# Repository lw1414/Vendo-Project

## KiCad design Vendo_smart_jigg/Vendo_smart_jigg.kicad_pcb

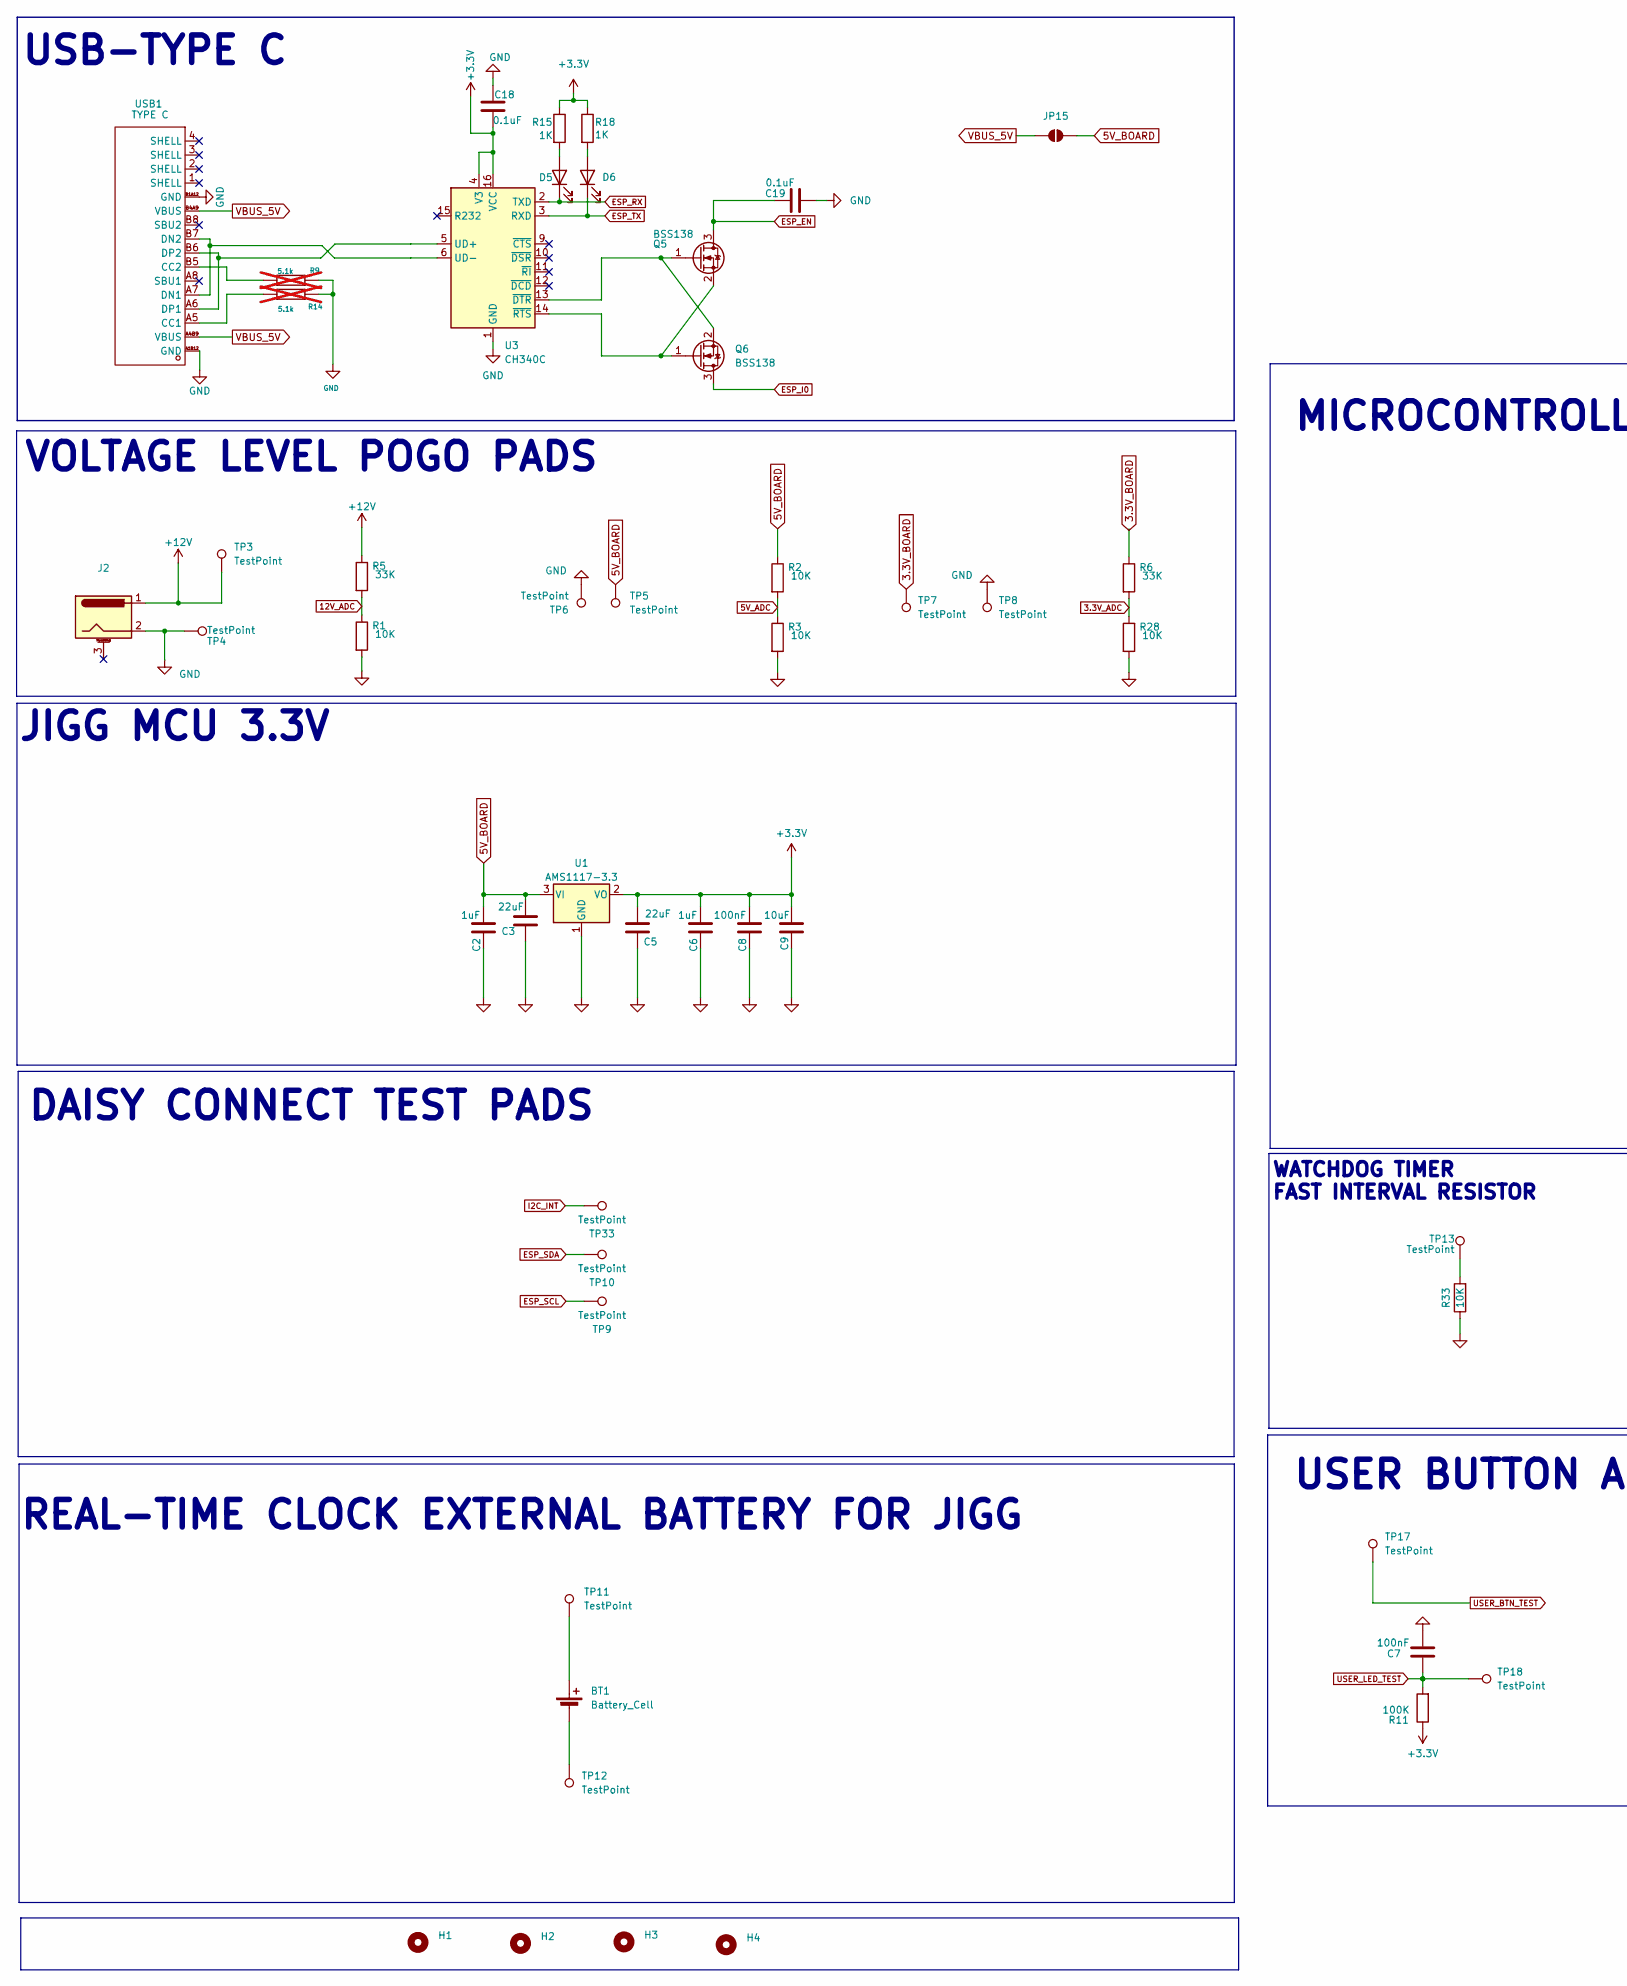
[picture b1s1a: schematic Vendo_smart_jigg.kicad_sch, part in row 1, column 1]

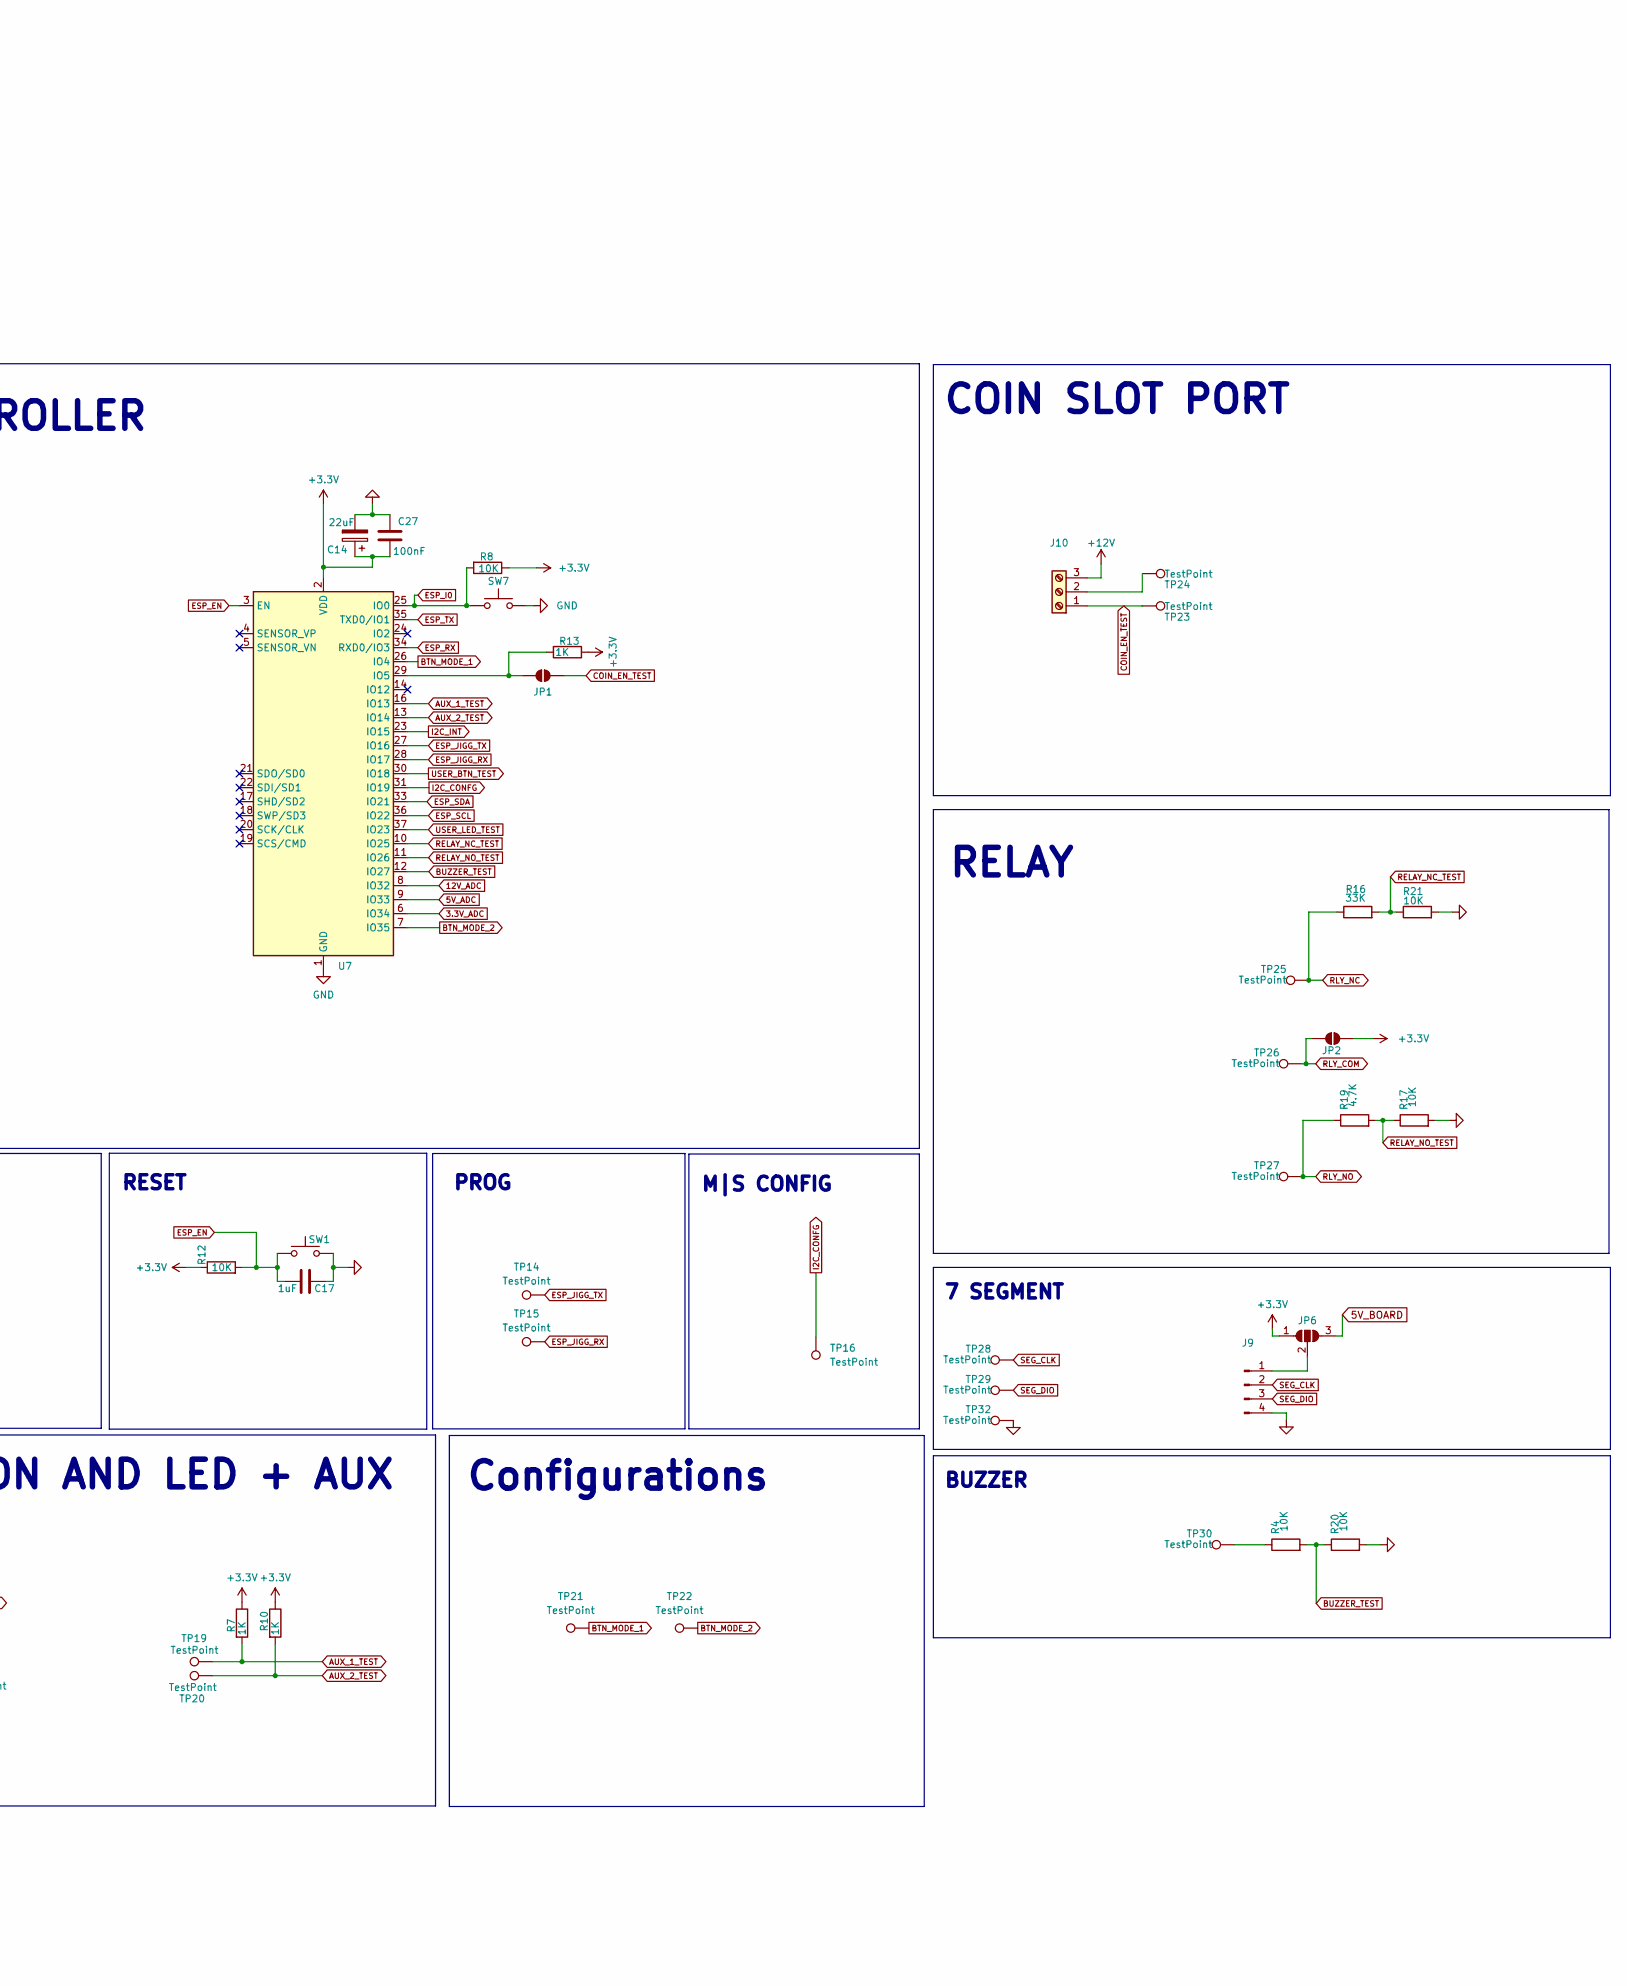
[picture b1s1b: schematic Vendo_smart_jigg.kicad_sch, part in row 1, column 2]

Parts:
BT1: Battery_Cell; BAT-TH_CR2032-BS-6-1; LCSC C969909
C2, C6: 1uF; C_0805_2012Metric_Pad1.18x1.45mm_HandSolder; LCSC C49678
C3, C5: 22uF; C_0603_1608Metric; LCSC C59461
C7, C8, C27: 100nF; C_0603_1608Metric_Pad1.08x0.95mm_HandSolder; LCSC C14663
C9: 10uF; C_0603_1608Metric_Pad1.08x0.95mm_HandSolder; LCSC C85713
C14: 22uF; C_0603_1608Metric_Pad1.08x0.95mm_HandSolder; LCSC C59461
C17: 1uF; C_0603_1608Metric_Pad1.08x0.95mm_HandSolder; LCSC C14663
C18: 0.1uF; C_0805_2012Metric_Pad1.18x1.45mm_HandSolder
C19: 0.1uF; C_0805_2012Metric_Pad1.18x1.45mm_HandSolder; LCSC C49678
D5, D6: LED; LED_0805_2012Metric_Pad1.15x1.40mm_HandSolder; LCSC C2297
H1, H2, H3, H4: MountingHole; MountingHole_3.2mm_M3_DIN965_Pad_TopBottom
J2: Barrel_Jack_MountingPin; BarrelJack_GCT_DCJ200-10-A_Horizontal
J9: Conn_01x04_Pin; JST_EH_B4B-EH-A_1x04_P2.50mm_Vertical
J10: Screw_Terminal_01x03; TerminalBlock_Xinya_XY308-2.54-3P_1x03_P2.54mm_Horizontal
JP1, JP2, JP15: SolderJumper_2_Open; PinHeader_1x02_P2.54mm_Vertical
JP6: SolderJumper_3_Open; SolderJumper-3_P1.3mm_Open_Pad1.0x1.5mm_NumberLabels
Q5, Q6: BSS138; SOT-23; LCSC C426569
R1, R2, R3, R4, R8, R12, R17, R20, R21, R28: 10K; R_0603_1608Metric_Pad0.98x0.95mm_HandSolder; LCSC C21190
R5, R6, R16: 33K; R_0603_1608Metric_Pad0.98x0.95mm_HandSolder; LCSC C21190
R7, R10, R13: 1K; R_0603_1608Metric_Pad0.98x0.95mm_HandSolder; LCSC C2960810
R9, R14: 5.1k; R_0603_1608Metric_Pad0.98x0.95mm_HandSolder; LCSC C103079; not fitted
R11: 100K; R_0603_1608Metric_Pad0.98x0.95mm_HandSolder; LCSC C105574
R15, R18: 1K; R_0603_1608Metric_Pad0.98x0.95mm_HandSolder; LCSC C21190
R19: 4.7K; R_0603_1608Metric_Pad0.98x0.95mm_HandSolder; LCSC C21190
R33: 10K; R_0603_1608Metric_Pad0.98x0.95mm_HandSolder; LCSC C2906982
SW1: SW_Push; SW_SPST_PTS645; LCSC C2689642
SW7: SW_Push; PinHeader_1x02_P2.54mm_Vertical; LCSC C2689642
TP3, TP4, TP5, TP6, TP7, TP8, TP9, TP10, TP11, TP12, TP13, TP16, TP17, TP18, TP19, TP20, TP21, TP22, TP23, TP24, TP25, TP26, TP27, TP30, TP32, TP33: TestPoint; TestPoint_Pad_D2.5mm
TP14, TP15, TP28, TP29: TestPoint; TestPoint_Pad_D1.5mm
U1: AMS1117-3.3; SOT-223-3_TabPin2; LCSC C5199435
U3: CH340C; SOP-16_3.9x9.9mm_P1.27mm; LCSC C84681
U7: ESP32-WROOM-32; ESP32-WROOM-32UE; LCSC C529577
USB1: TYPE C; USB-C-SMD_TYPE-C16PIN; Manufacturer Part TYPE-C16PIN; LCSC Part Name Type-C 母 卧贴

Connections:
3.3V_ADC: R6.2, R28.1, U7.6 (IO34)
3.3V_BOARD: R6.1, TP7.1
5V_ADC: R2.2, R3.1, U7.9 (IO33)
5V_BOARD: C2.2, C3.2, JP6.3 (B), JP15.1 (A), R2.1, TP5.1, U1.3 (VI)
12V_ADC: R1.1, R5.2, U7.8 (IO32)
+3.3V: C5.2, C6.2, C8.2, C9.2, C14.1, C18.1, C27.1, JP2.2 (B), JP6.1 (A), R7.1, R8.1, R10.1, R11.1, R12.1, R13.1, R15.1, R18.1, U1.2 (VO), U3.4 (V3), U3.16 (VCC), U7.2 (VDD)
+12V: J2.1, J10.3, R5.1, TP3.1
AUX_1_TEST: R7.2, TP19.1, U7.16 (IO13)
AUX_2_TEST: R10.2, TP20.1, U7.13 (IO14)
BTN_MODE_1: TP21.1, U7.26 (IO4)
BTN_MODE_2: TP22.1, U7.7 (IO35)
BUZZER_TEST: R4.2, R20.1, U7.12 (IO27)
COIN_EN_TEST: J10.1, JP1.1 (A), TP23.1
ESP_EN: C17.2, C19.2, Q5.3 (D), R12.2, SW1.1, U7.3 (EN)
ESP_I0: Q6.3 (D), R8.2, SW7.1, U7.25 (IO0)
ESP_JIGG_RX: TP15.1, U7.28 (IO17)
ESP_JIGG_TX: TP14.1, U7.27 (IO16)
ESP_RX: D5.1 (K), U3.2 (TXD), U7.34 (RXD0/IO3)
ESP_SCL: TP9.1, U7.36 (IO22)
ESP_SDA: TP10.1, U7.33 (IO21)
ESP_TX: D6.1 (K), U3.3 (RXD), U7.35 (TXD0/IO1)
GND: C2.1, C3.1, C5.1, C6.1, C7.1, C8.1, C9.1, C14.2, C17.1, C18.2, C19.1, C27.2, J2.2, J9.4, R1.2, R3.2, R9.2, R14.2, R17.2, R20.2, R21.2, R28.2, R33.1, SW1.2, SW7.2, TP4.1, TP6.1, TP8.1, TP32.1, U1.1 (GND), U3.1 (GND), U7.1 (GND), U7.15 (GND), U7.38 (GND), U7.39 (GND), USB1.A1B12 (GND), USB1.B1A12 (GND)
I2C_CONFG: TP16.1, U7.31 (IO19)
I2C_INT: TP33.1, U7.23 (IO15)
unnamed: BT1.1 (+), TP11.1
unnamed: BT1.2 (-), TP12.1
unnamed: D5.2 (A), R15.2
unnamed: D6.2 (A), R18.2
unnamed: J9.1, JP6.2 (C)
unnamed: J10.2, TP24.1
unnamed: JP1.2 (B), R13.2, U7.29 (IO5)
unnamed: Q5.1 (G), Q6.2 (S), U3.13 (~DTR)
unnamed: Q5.2 (S), Q6.1 (G), U3.14 (~RTS)
unnamed: R4.1, TP30.1
unnamed: R33.2, TP13.1
unnamed: U3.5 (UD+), USB1.A6 (DP1), USB1.B6 (DP2)
unnamed: U3.6 (UD-), USB1.A7 (DN1), USB1.B7 (DN2)
unnamed: R14.1, USB1.A5 (CC1)
unnamed: R9.1, USB1.B5 (CC2)
RELAY_NC_TEST: R16.2, R21.1, U7.10 (IO25)
RELAY_NO_TEST: R17.1, R19.2, U7.11 (IO26)
RLY_COM: JP2.1 (A), TP26.1
RLY_NC: R16.1, TP25.1
RLY_NO: R19.1, TP27.1
SEG_CLK: J9.2, TP28.1
SEG_DIO: J9.3, TP29.1
USER_BTN_TEST: TP17.1, U7.30 (IO18)
USER_LED_TEST: C7.2, R11.2, TP18.1, U7.37 (IO23)
VBUS_5V: JP15.2 (B), USB1.A4B9 (VBUS), USB1.B4A9 (VBUS)

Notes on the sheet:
DAISY CONNECT TEST PADS
WATCHDOG TIMER FAST INTERVAL RESISTOR
USER BUTTON AND LED + AUX
COIN SLOT PORT
M|S CONFIG
RESET
VOLTAGE LEVEL POGO PADS
7 SEGMENT
Configurations
PROG
RELAY
MICROCONTROLLER
REAL-TIME CLOCK EXTERNAL BATTERY FOR JIGG
BUZZER
JIGG MCU 3.3V
USB-TYPE C

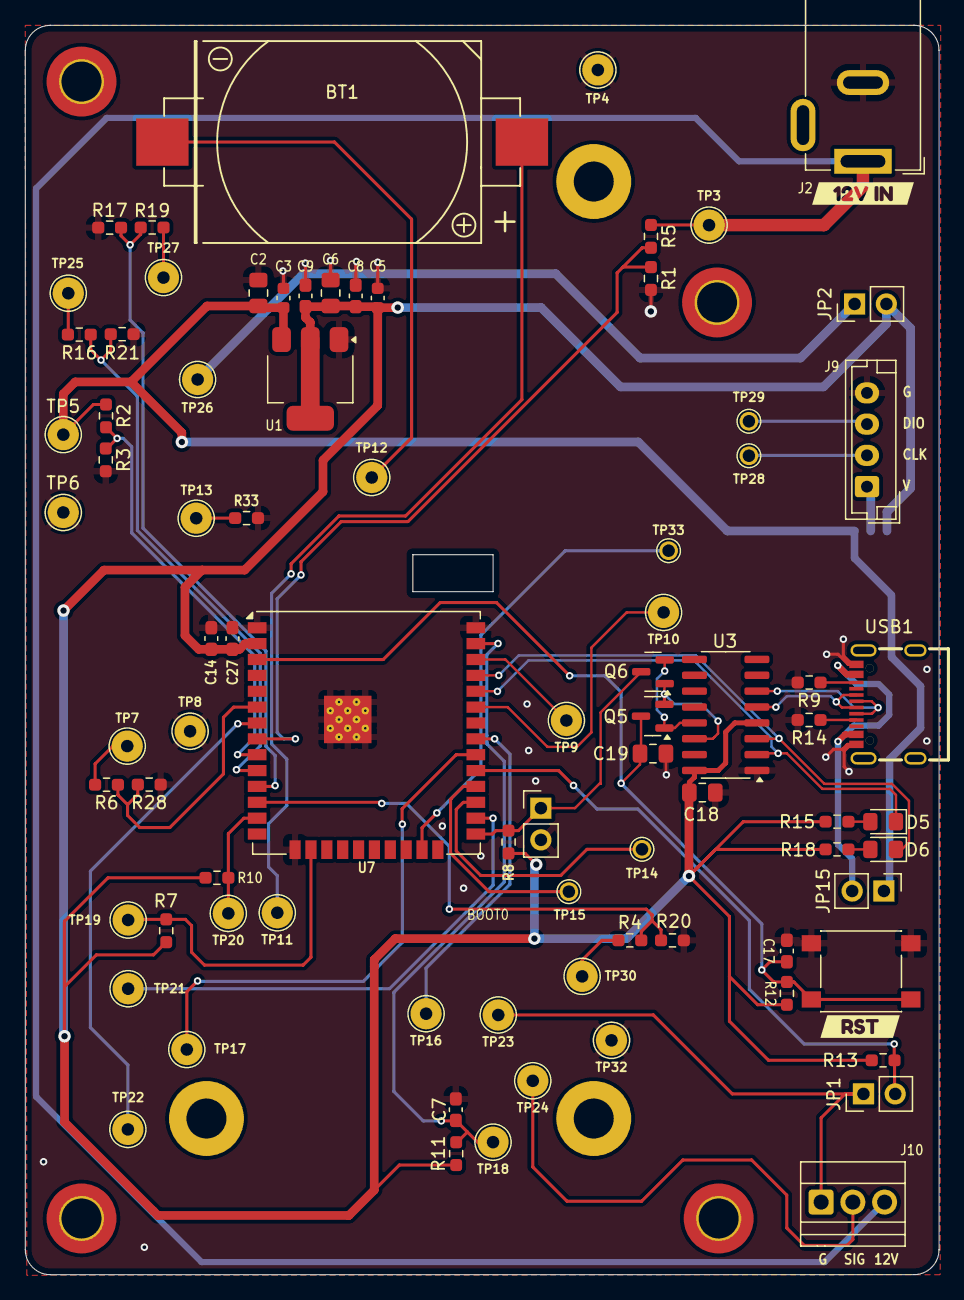
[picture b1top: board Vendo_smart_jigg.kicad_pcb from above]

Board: 2 copper layers, 73.1 x 100.0 mm, 89 parts (1 on the bottom side), 49 nets.

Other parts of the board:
kibuzzard-6A0C536D: G***; kibuzzard-6A0C536D
kibuzzard-6A0C5003: G***; kibuzzard-6A0C5003

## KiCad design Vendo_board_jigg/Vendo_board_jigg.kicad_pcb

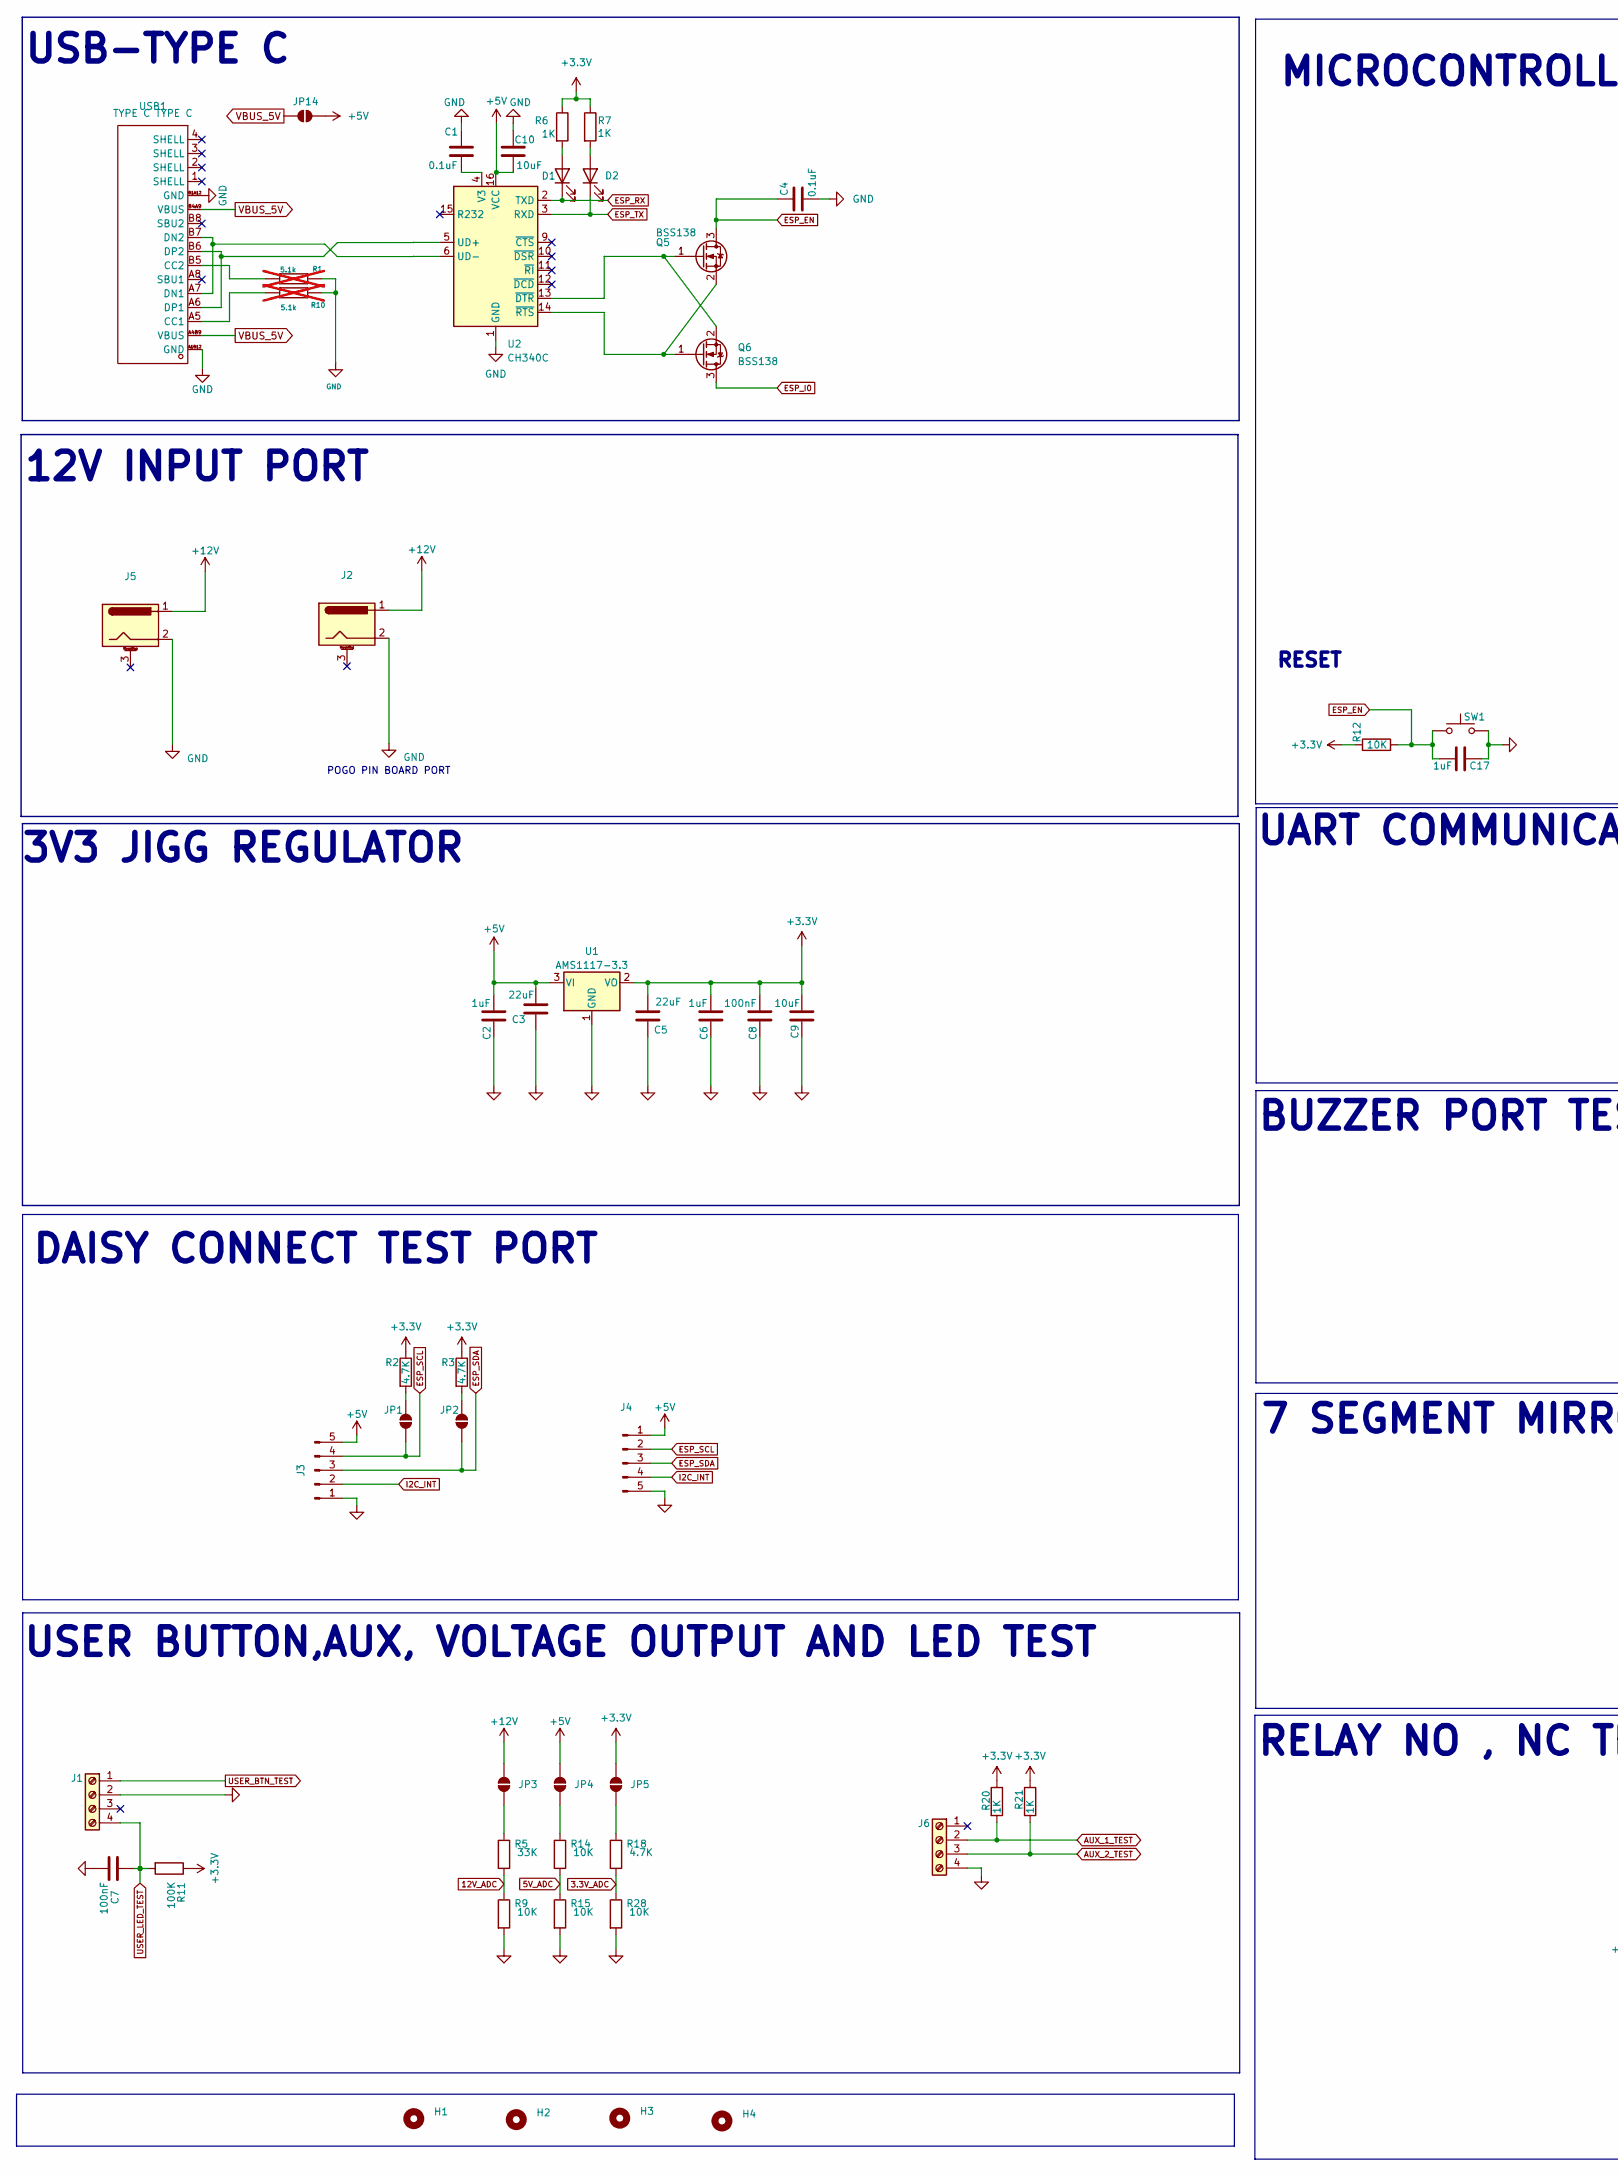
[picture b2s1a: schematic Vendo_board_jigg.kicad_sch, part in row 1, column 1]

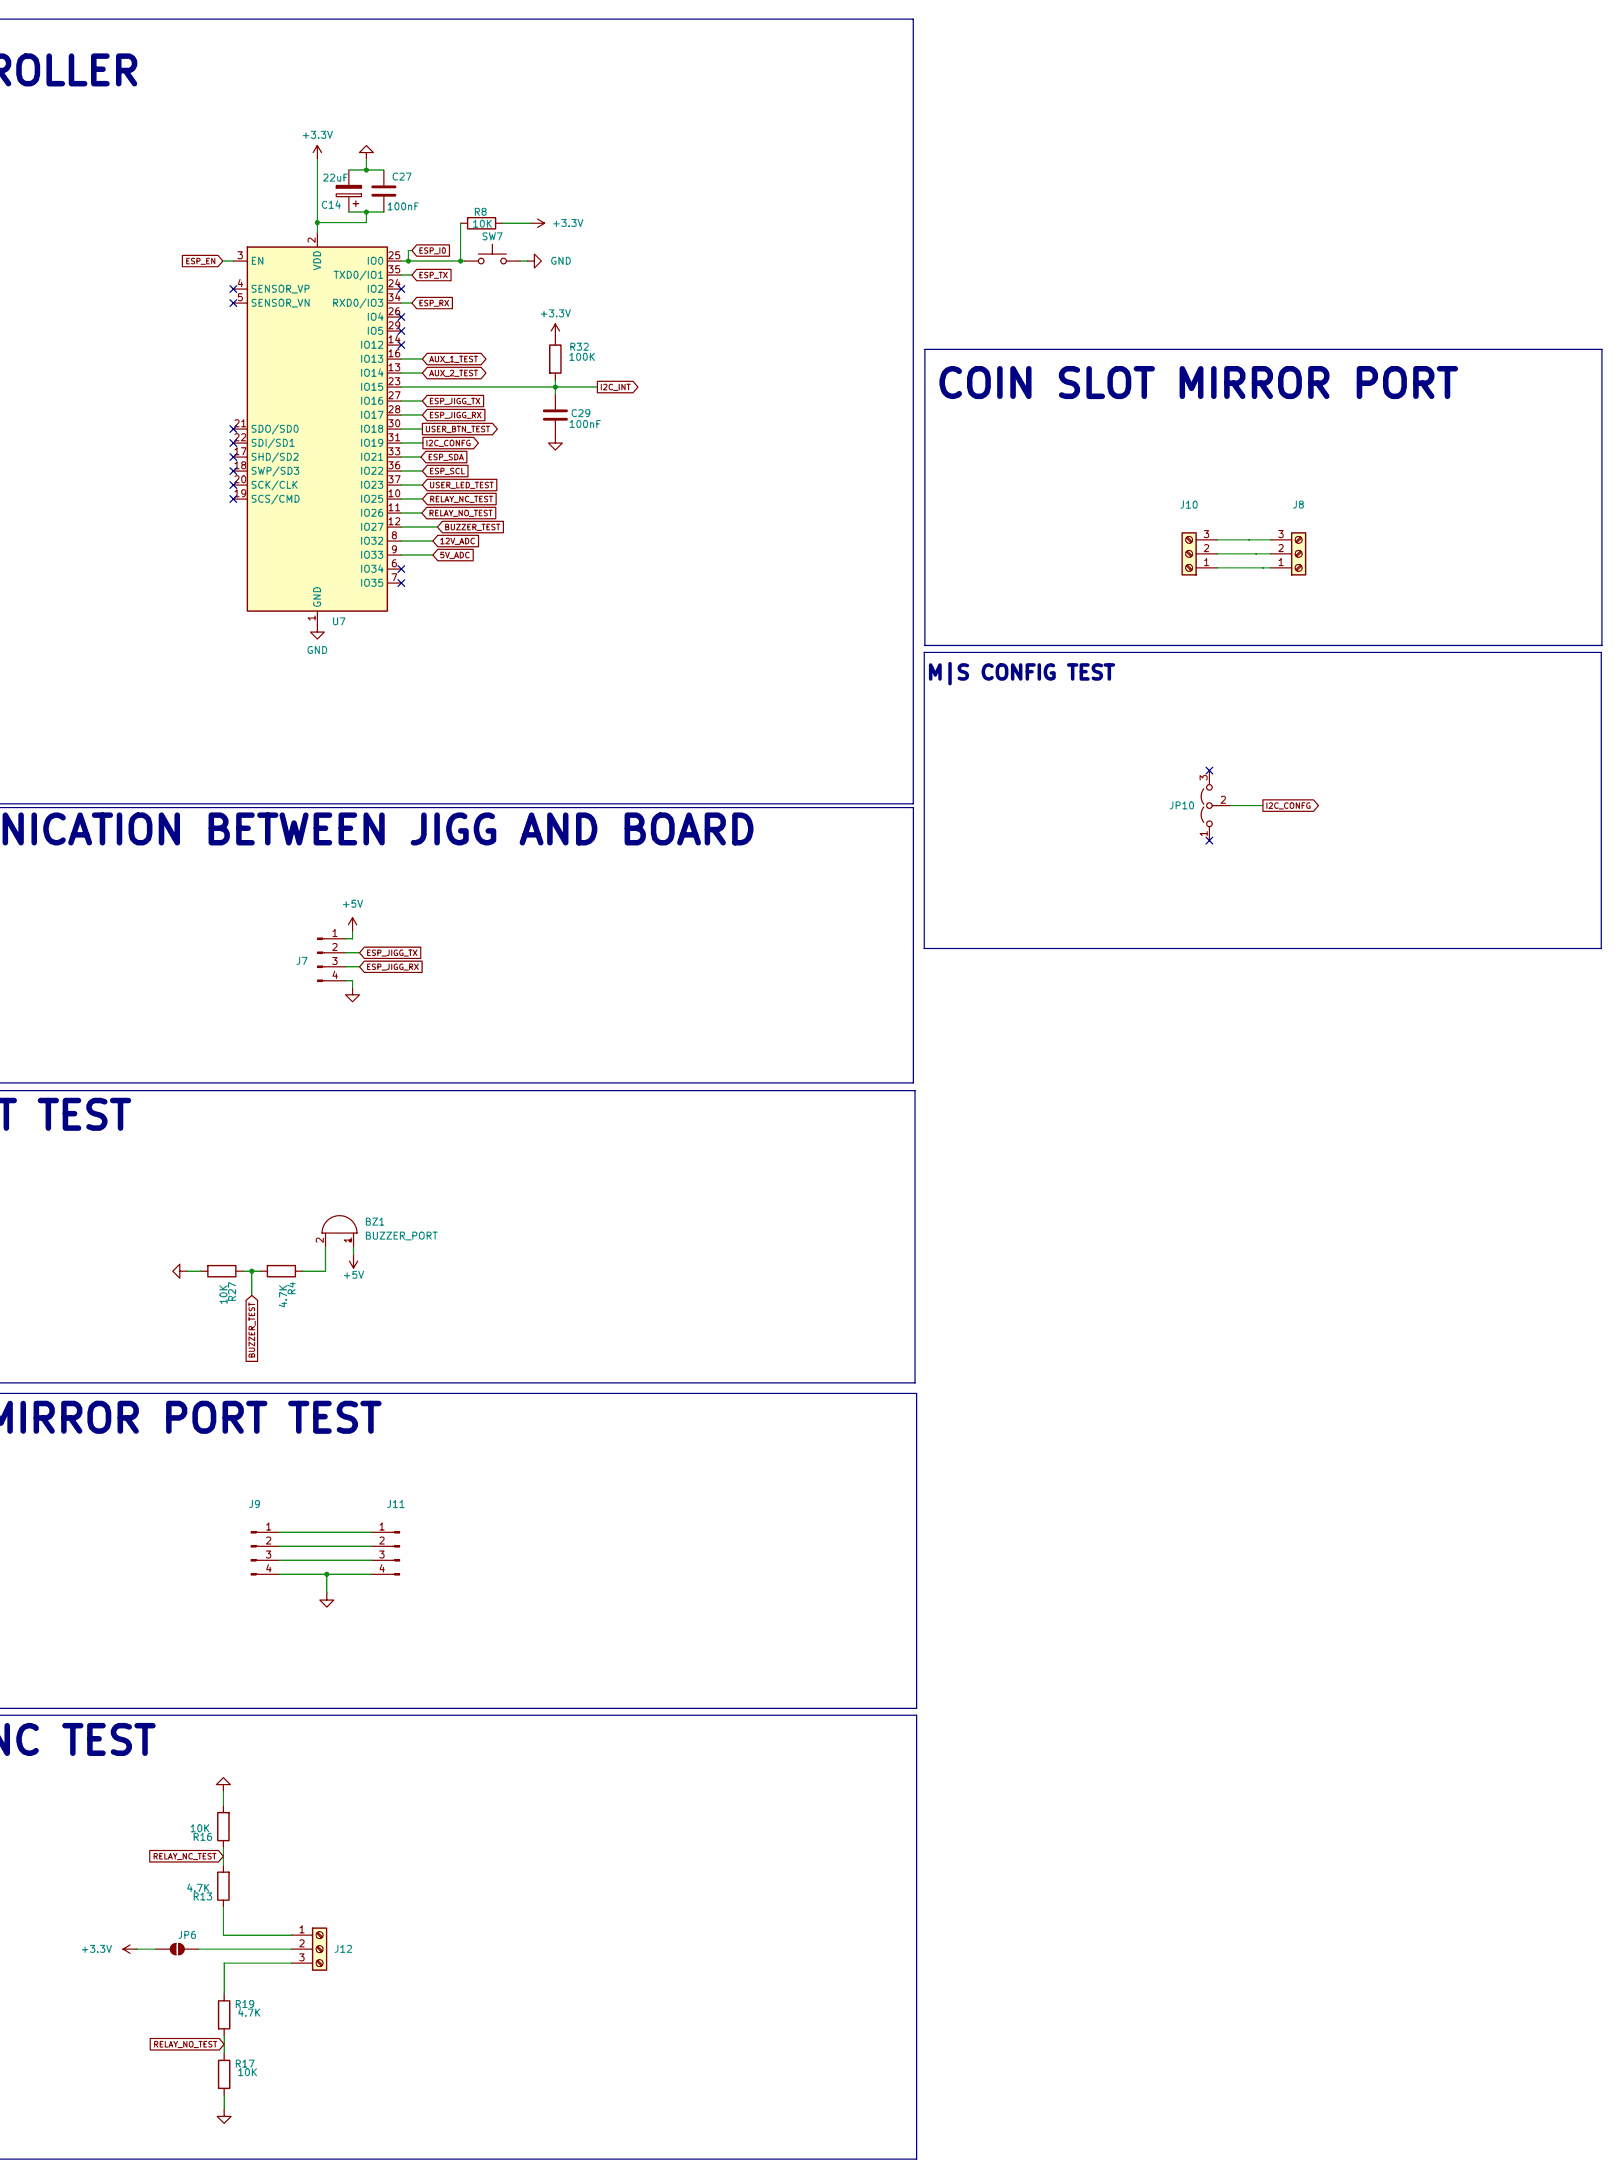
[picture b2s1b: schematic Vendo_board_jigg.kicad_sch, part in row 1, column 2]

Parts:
BZ1: BUZZER_PORT; Buzzer_12x9.5RM7.6
C1, C4: 0.1uF; C_0805_2012Metric_Pad1.18x1.45mm_HandSolder; LCSC C49678
C2, C6: 1uF; C_0805_2012Metric_Pad1.18x1.45mm_HandSolder; LCSC C49678
C3, C5: 22uF; C_0603_1608Metric; LCSC C59461
C7, C8, C27, C29: 100nF; C_0603_1608Metric_Pad1.08x0.95mm_HandSolder; LCSC C14663
C9: 10uF; C_0603_1608Metric_Pad1.08x0.95mm_HandSolder; LCSC C85713
C10: 10uF; C_0805_2012Metric_Pad1.18x1.45mm_HandSolder; LCSC C15850
C14: 22uF; C_0603_1608Metric_Pad1.08x0.95mm_HandSolder; LCSC C59461
C17: 1uF; C_0603_1608Metric_Pad1.08x0.95mm_HandSolder; LCSC C14663
D1, D2: LED; LED_0805_2012Metric_Pad1.15x1.40mm_HandSolder; LCSC C2297
H1, H2, H3, H4: MountingHole; MountingHole_3.2mm_M3_DIN965_Pad_TopBottom
J1, J6: Screw_Terminal_01x04; TerminalBlock_Xinya_XY308-2.54-4P_1x04_P2.54mm_Horizontal
J2, J5: Barrel_Jack_MountingPin; BarrelJack_GCT_DCJ200-10-A_Horizontal
J3, J4: Conn_01x05_Pin; JST_EH_B5B-EH-A_1x05_P2.50mm_Vertical
J7: FTDI; PinHeader_1x04_P2.54mm_Vertical
J8, J10: Screw_Terminal_01x03; TerminalBlock_Xinya_XY308-2.54-3P_1x03_P2.54mm_Horizontal
J9, J11: Conn_01x04_Pin; JST_EH_B4B-EH-A_1x04_P2.50mm_Vertical
J12: Screw_Terminal_01x03; TerminalBlock_MetzConnect_Type073_RT02603HBLU_1x03_P5.08mm_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
JP1, JP2: SolderJumper_2_Open; SolderJumper-2_P1.3mm_Open_RoundedPad1.0x1.5mm
JP3, JP4, JP5, JP6, JP14: SolderJumper_2_Open; PinHeader_1x02_P2.54mm_Vertical
JP10: Jumper_3_Open; PinHeader_1x03_P2.54mm_Vertical
Q5, Q6: BSS138; SOT-23; LCSC C426569
R1, R10: 5.1k; R_0603_1608Metric_Pad0.98x0.95mm_HandSolder; LCSC C103079; not fitted
R2, R3: 4.7K; R_0603_1608Metric_Pad0.98x0.95mm_HandSolder; LCSC C2960810
R4, R13, R18, R19: 4.7K; R_0603_1608Metric_Pad0.98x0.95mm_HandSolder; LCSC C21190
R5: 33K; R_0603_1608Metric_Pad0.98x0.95mm_HandSolder; LCSC C21190
R6, R7: 1K; R_0603_1608Metric_Pad0.98x0.95mm_HandSolder; LCSC C21190
R8, R9, R12, R14, R15, R16, R17, R27, R28: 10K; R_0603_1608Metric_Pad0.98x0.95mm_HandSolder; LCSC C21190
R11, R32: 100K; R_0603_1608Metric_Pad0.98x0.95mm_HandSolder; LCSC C105574
R20, R21: 1K; R_0603_1608Metric_Pad0.98x0.95mm_HandSolder; LCSC C2960810
SW1: SW_Push; SW_SPST_PTS645; LCSC C2689642
SW7: SW_Push; PinHeader_1x02_P2.54mm_Vertical; LCSC C2689642
U1: AMS1117-3.3; SOT-223-3_TabPin2; LCSC C5199435
U2: CH340C; SOP-16_3.9x9.9mm_P1.27mm; LCSC C84681
U7: ESP32-WROOM-32; ESP32-WROOM-32UE; LCSC C529577
USB1: TYPE C TYPE C; USB-C-SMD_TYPE-C16PIN; Manufacturer Part TYPE-C16PIN; LCSC Part Name Type-C 母 卧贴

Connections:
3.3V_ADC: R18.2, R28.1
5V_ADC: R14.2, R15.1, U7.9 (IO33)
12V_ADC: R5.2, R9.1, U7.8 (IO32)
+3.3V: C5.2, C6.2, C8.2, C9.2, C14.1, C27.1, JP5.2 (B), JP6.2 (B), R2.1, R3.1, R6.1, R7.1, R8.1, R11.1, R12.1, R20.1, R21.1, R32.1, U1.2 (VO), U7.2 (VDD)
+5V: BZ1.1 (+), C2.2, C3.2, C10.1, J3.5, J4.1, J7.1, JP4.2 (B), JP14.2 (B), U1.3 (VI), U2.16 (VCC)
+12V: J2.1, J5.1, JP3.2 (B)
AUX_1_TEST: J6.2, R20.2, U7.16 (IO13)
AUX_2_TEST: J6.3, R21.2, U7.13 (IO14)
BUZZER_TEST: R4.2, R27.1, U7.12 (IO27)
ESP_EN: C4.2, C17.2, Q5.3 (D), R12.2, SW1.1, U7.3 (EN)
ESP_I0: Q6.3 (D), R8.2, SW7.1, U7.25 (IO0)
ESP_JIGG_RX: J7.3, U7.28 (IO17)
ESP_JIGG_TX: J7.2, U7.27 (IO16)
ESP_RX: D1.1 (K), U2.2 (TXD), U7.34 (RXD0/IO3)
ESP_SCL: J3.4, J4.2, JP1.1 (A), U7.36 (IO22)
ESP_SDA: J3.3, J4.3, JP2.1 (A), U7.33 (IO21)
ESP_TX: D2.1 (K), U2.3 (RXD), U7.35 (TXD0/IO1)
GND: C1.2, C2.1, C3.1, C4.1, C5.1, C6.1, C7.1, C8.1, C9.1, C10.2, C14.2, C17.1, C27.2, C29.1, J1.2, J2.2, J3.1, J4.5, J5.2, J6.4, J7.4, J9.4, J11.4, R1.2, R9.2, R10.2, R15.2, R16.2, R17.2, R27.2, R28.2, SW1.2, SW7.2, U1.1 (GND), U2.1 (GND), U7.1 (GND), U7.15 (GND), U7.38 (GND), U7.39 (GND), USB1.A1B12 (GND), USB1.B1A12 (GND)
I2C_CONFG: JP10.2 (C), U7.31 (IO19)
I2C_INT: C29.2, J3.2, J4.4, R32.2, U7.23 (IO15)
unnamed: BZ1.2 (-), R4.1
unnamed: D1.2 (A), R6.2
unnamed: D2.2 (A), R7.2
unnamed: J8.1, J10.1
unnamed: J8.2, J10.2
unnamed: J8.3, J10.3
unnamed: J9.1, J11.1
unnamed: J9.2, J11.2
unnamed: J9.3, J11.3
unnamed: J12.1, R13.1
unnamed: J12.2, JP6.1 (A)
unnamed: J12.3, R19.1
unnamed: JP1.2 (B), R2.2
unnamed: JP2.2 (B), R3.2
unnamed: JP3.1 (A), R5.1
unnamed: JP4.1 (A), R14.1
unnamed: JP5.1 (A), R18.1
unnamed: Q5.1 (G), Q6.2 (S), U2.13 (~DTR)
unnamed: Q5.2 (S), Q6.1 (G), U2.14 (~RTS)
unnamed: U2.5 (UD+), USB1.A6 (DP1), USB1.B6 (DP2)
unnamed: U2.6 (UD-), USB1.A7 (DN1), USB1.B7 (DN2)
unnamed: C1.1, U2.4 (V3)
unnamed: R10.1, USB1.A5 (CC1)
unnamed: R1.1, USB1.B5 (CC2)
RELAY_NC_TEST: R13.2, R16.1, U7.10 (IO25)
RELAY_NO_TEST: R17.1, R19.2, U7.11 (IO26)
USER_BTN_TEST: J1.1, U7.30 (IO18)
USER_LED_TEST: C7.2, J1.4, R11.2, U7.37 (IO23)
VBUS_5V: JP14.1 (A), USB1.A4B9 (VBUS), USB1.B4A9 (VBUS)

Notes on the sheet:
DAISY CONNECT TEST PORT
USER BUTTON,AUX, VOLTAGE OUTPUT AND LED TEST
USB-TYPE C
COIN SLOT MIRROR PORT
RESET
12V INPUT PORT
POGO PIN BOARD PORT
7 SEGMENT MIRROR PORT TEST
UART COMMUNICATION BETWEEN JIGG AND BOARD
3V3 JIGG REGULATOR
M|S CONFIG TEST
RELAY NO , NC TEST
MICROCONTROLLER
BUZZER PORT TEST

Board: 2 copper layers, 81 parts (2 on the bottom side), 49 nets, no tracks yet.

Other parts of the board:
kibuzzard-6A0C4ED1: G***; kibuzzard-6A0C4ED1
kibuzzard-6A0C4EDA: G***; kibuzzard-6A0C4EDA
kibuzzard-6A0C4EE4: G***; kibuzzard-6A0C4EE4
kibuzzard-6A0C5E83: G***; kibuzzard-6A0C5E83
kibuzzard-6A0C5E89: G***; kibuzzard-6A0C5E89
kibuzzard-6A0C5E92: G***; kibuzzard-6A0C5E92
kibuzzard-6A0C536D: G***; kibuzzard-6A0C536D
kibuzzard-6A0C5003: G***; kibuzzard-6A0C5003
